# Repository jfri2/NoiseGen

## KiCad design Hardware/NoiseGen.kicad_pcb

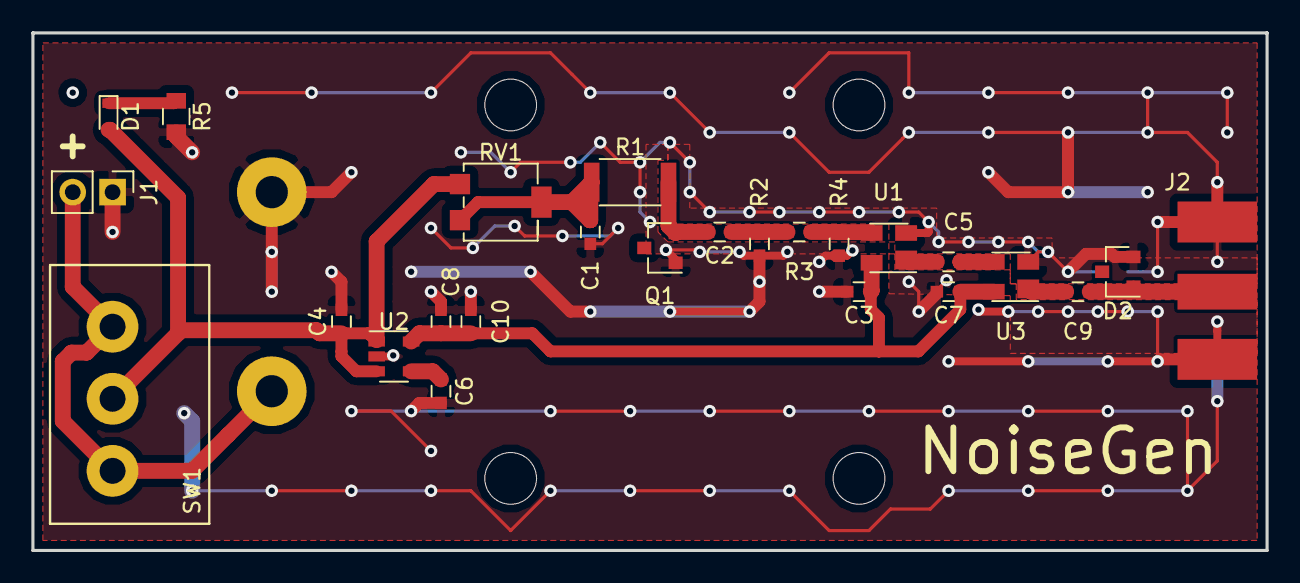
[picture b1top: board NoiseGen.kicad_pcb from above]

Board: 2 copper layers, 78.7 x 33.0 mm, 26 parts (1 on the bottom side), 14 nets.

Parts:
BT1: 9V; 1294
C1: 1nF; C_0603
C2, C5, C9: 100pF; C_0603
C3, C6, C7: 100nF; C_0603
C4, C8, C10: 1uF; C_0603
D1: RED; D_0603
D2: CM1214A; SOT-23
J1: CONN_01X02; Pin_Header_Straight_1x02_Pitch2.54mm
J2: SMA; J502
Q1: BFR92; SOT-23
R1: 51R; R_2010
R2, R4: 120R; C_0603
R3: 56R; C_0603
R5: 680R; C_0805
RV1: 1k; Potentiometer_Trimmer_Bourns_3214G
SW1: SPST; GF-123-0054
U1, U3: MAX2650; SOT-143
U2: AP2210; SOT-23-5

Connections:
+5V: C3.1, C7.1, C8.1, C10.1, U1.4, U2.5, U3.4
+9V: C4.1, D1.2, RV1.3, SW1.2, U2.1, U2.3
GND: BT1.2, C1.2, C3.2, C4.2, C6.2, C7.2, C8.2, C10.2, D2.2, J1.1, J2.2, Q1.1, R2.2, R4.2, R5.2, U1.2, U2.2, U3.2
unnamed: BT1.1, J1.2, SW1.1
unnamed: C1.1, R1.1, RV1.1, RV1.2
unnamed: C2.1, R2.1, R3.2
unnamed: C2.2, Q1.2, R1.2
unnamed: C5.1, U3.3
unnamed: C5.2, U1.1
unnamed: C6.1, U2.4
unnamed: C9.1, D2.1, J2.1
unnamed: C9.2, U3.1
unnamed: D1.1, R5.1
unnamed: R3.1, R4.1, U1.3

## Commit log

2017-08-13 Finished schematic & BOM
2017-08-13 Finshed board layout
2017-08-13 Added text to PCB, cleaned up PCB
2017-08-14 Add TVS diode
2017-08-14 Updated schematic
2017-08-15 Generated Gerbers
